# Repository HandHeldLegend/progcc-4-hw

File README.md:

# progcc-4-hw
Official repository for ProGCC 4 Hardware.

## 3D Models License
<br />The 3D CAD files are licensed under a <a rel="license" href="http://creativecommons.org/licenses/by/4.0/">Creative Commons Attribution 4.0 International License</a>.

## Schematic and PCB License
<br />This PCB and electronic schematic are licensed under a <a rel="license" href="http://creativecommons.org/licenses/by-nc-sa/3.0/">Creative Commons Attribution-NonCommercial-ShareAlike 3.0 Unported License</a>.

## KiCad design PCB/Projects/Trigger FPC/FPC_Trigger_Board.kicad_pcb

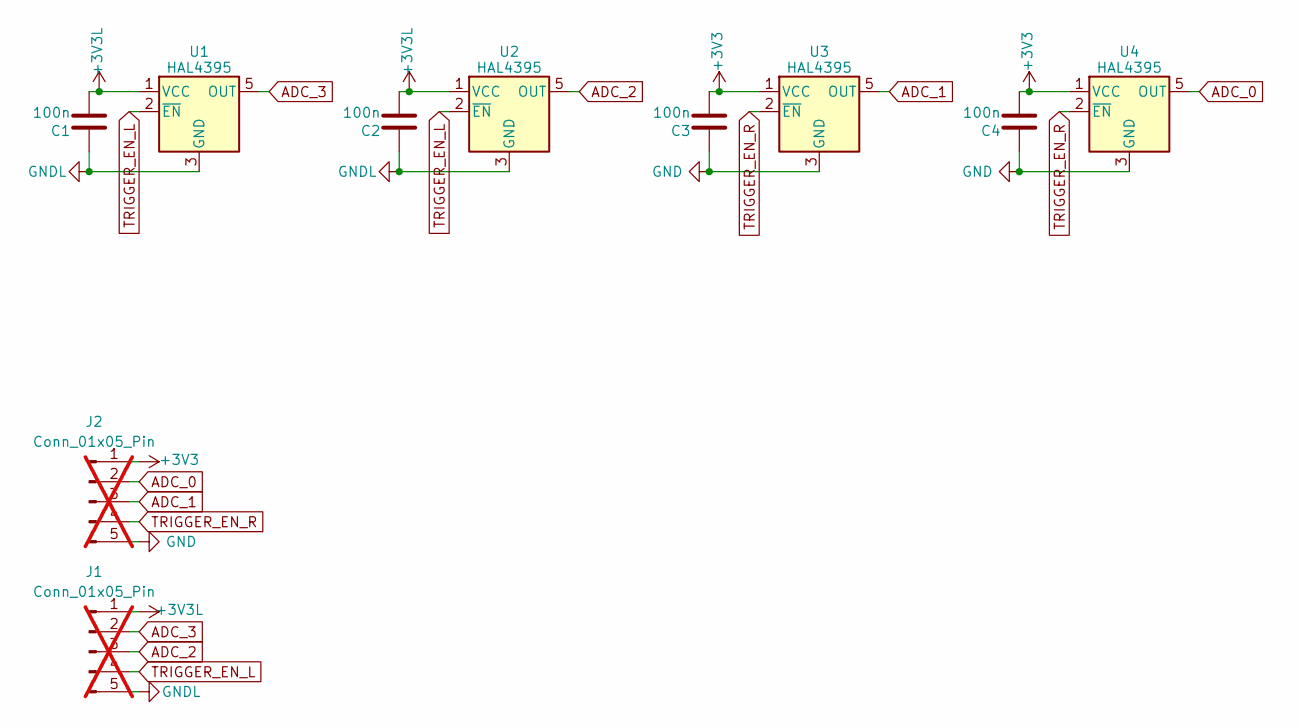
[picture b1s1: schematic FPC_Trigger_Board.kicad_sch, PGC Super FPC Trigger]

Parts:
C1, C2, C3, C4: 100n; C_0201_0603Metric; MPN GRM033R61A104KE15D; LCSC C76934
J1, J2: Conn_01x05_Pin; 505110-0592 Ribbon; not fitted
U1, U2, U3, U4: HAL4395; SOT-23-5L; MPN HAL4395SO5; LCSC C49165022

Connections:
+3V3: C3.2, C4.2, J2.1, U3.1 (VCC), U4.1 (VCC)
+3V3L: C1.2, C2.2, J1.1, U1.1 (VCC), U2.1 (VCC)
ADC_0: J2.2, U4.5 (OUT)
ADC_1: J2.3, U3.5 (OUT)
ADC_2: J1.3, U2.5 (OUT)
ADC_3: J1.2, U1.5 (OUT)
GND: C3.1, C4.1, J2.5, U3.3 (GND), U4.3 (GND)
GNDL: C1.1, C2.1, J1.5, U1.3 (GND), U2.3 (GND)
TRIGGER_EN_L: J1.4, U1.2 (~EN), U2.2 (~EN)
TRIGGER_EN_R: J2.4, U3.2 (~EN), U4.2 (~EN)

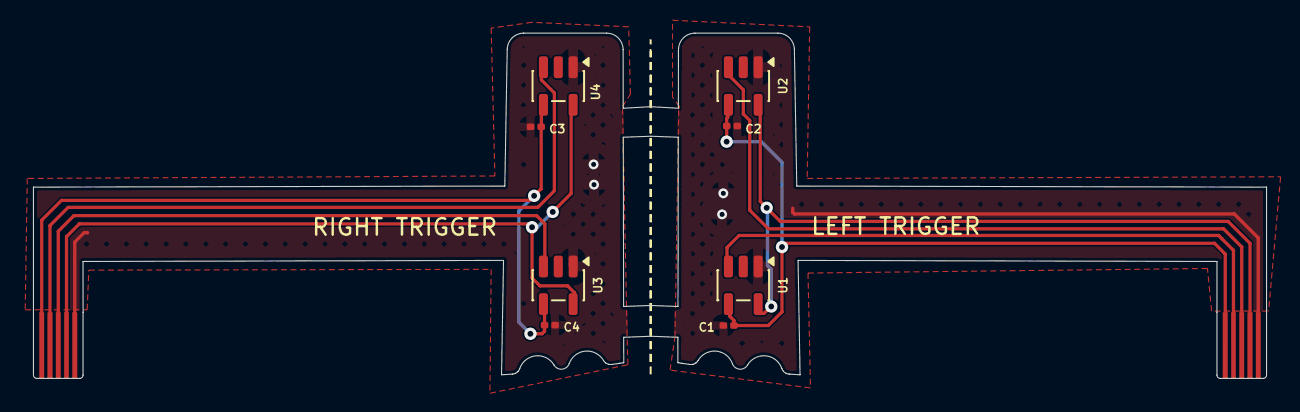
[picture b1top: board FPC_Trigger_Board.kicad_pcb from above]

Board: 2 copper layers, 74.6 x 20.9 mm, 10 parts (2 on the bottom side), 10 nets.

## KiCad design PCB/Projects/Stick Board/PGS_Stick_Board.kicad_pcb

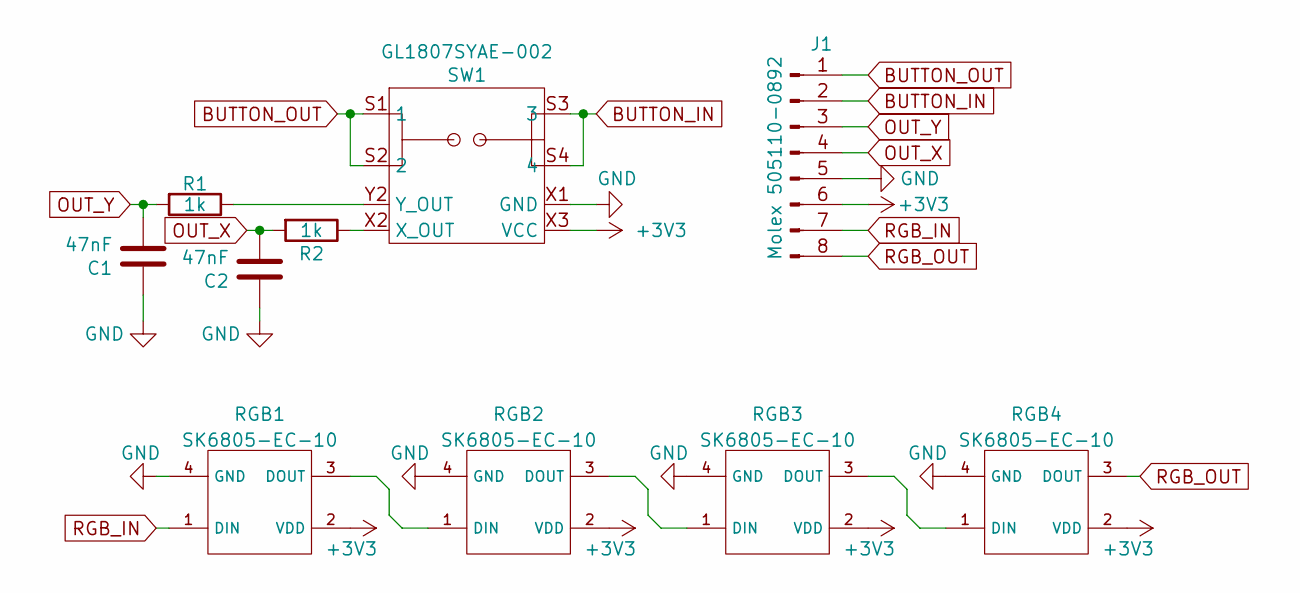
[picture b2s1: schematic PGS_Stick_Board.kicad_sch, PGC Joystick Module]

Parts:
C1, C2: 47nF; C_0402_1005Metric; MPN CC0402KRX7R9BB473; LCSC C272875
J1: Molex 505110-0892; 5051100892; MPN 505110-0892; LCSC C5902847
R1, R2: 1k; R_0201_0603Metric; MPN RC0201FR-071KL; LCSC C138165
RGB1, RGB2, RGB3, RGB4: SK6805-EC-10; MPN SK6805-EC-10; LCSC C22394946
SW1: GL1807SYAE-002; GL1807SYAE; MPN GL1807SYAE-002

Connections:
+3V3: J1.6, RGB1.2 (VDD), RGB2.2 (VDD), RGB3.2 (VDD), RGB4.2 (VDD), SW1.X3 (VCC), SW1.Y3 (VCC)
BUTTON_IN: J1.2, SW1.S3 (3), SW1.S4 (4)
BUTTON_OUT: J1.1, SW1.S1 (1), SW1.S2 (2)
GND: C1.1, C2.1, J1.5, RGB1.4 (GND), RGB2.4 (GND), RGB3.4 (GND), RGB4.4 (GND), SW1.X1 (GND), SW1.Y1 (GND)
unnamed: RGB1.3 (DOUT), RGB2.1 (DIN)
unnamed: RGB2.3 (DOUT), RGB3.1 (DIN)
unnamed: RGB3.3 (DOUT), RGB4.1 (DIN)
unnamed: R2.1, SW1.X2 (X_OUT)
unnamed: R1.1, SW1.Y2 (Y_OUT)
OUT_X: C2.2, J1.4, R2.2
OUT_Y: C1.2, J1.3, R1.2
RGB_IN: J1.7, RGB1.1 (DIN)
RGB_OUT: J1.8, RGB4.3 (DOUT)

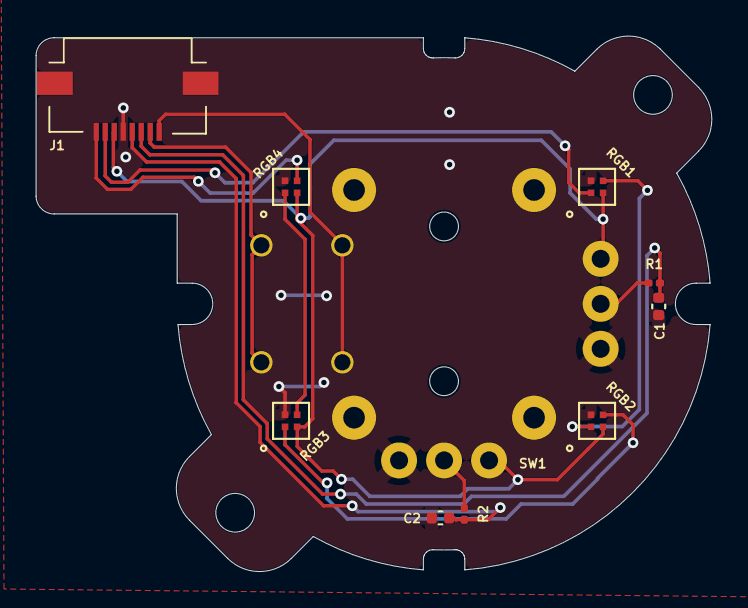
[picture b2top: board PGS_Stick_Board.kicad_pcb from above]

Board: 2 copper layers, 37.5 x 29.7 mm, 10 parts (0 on the bottom side), 13 nets.

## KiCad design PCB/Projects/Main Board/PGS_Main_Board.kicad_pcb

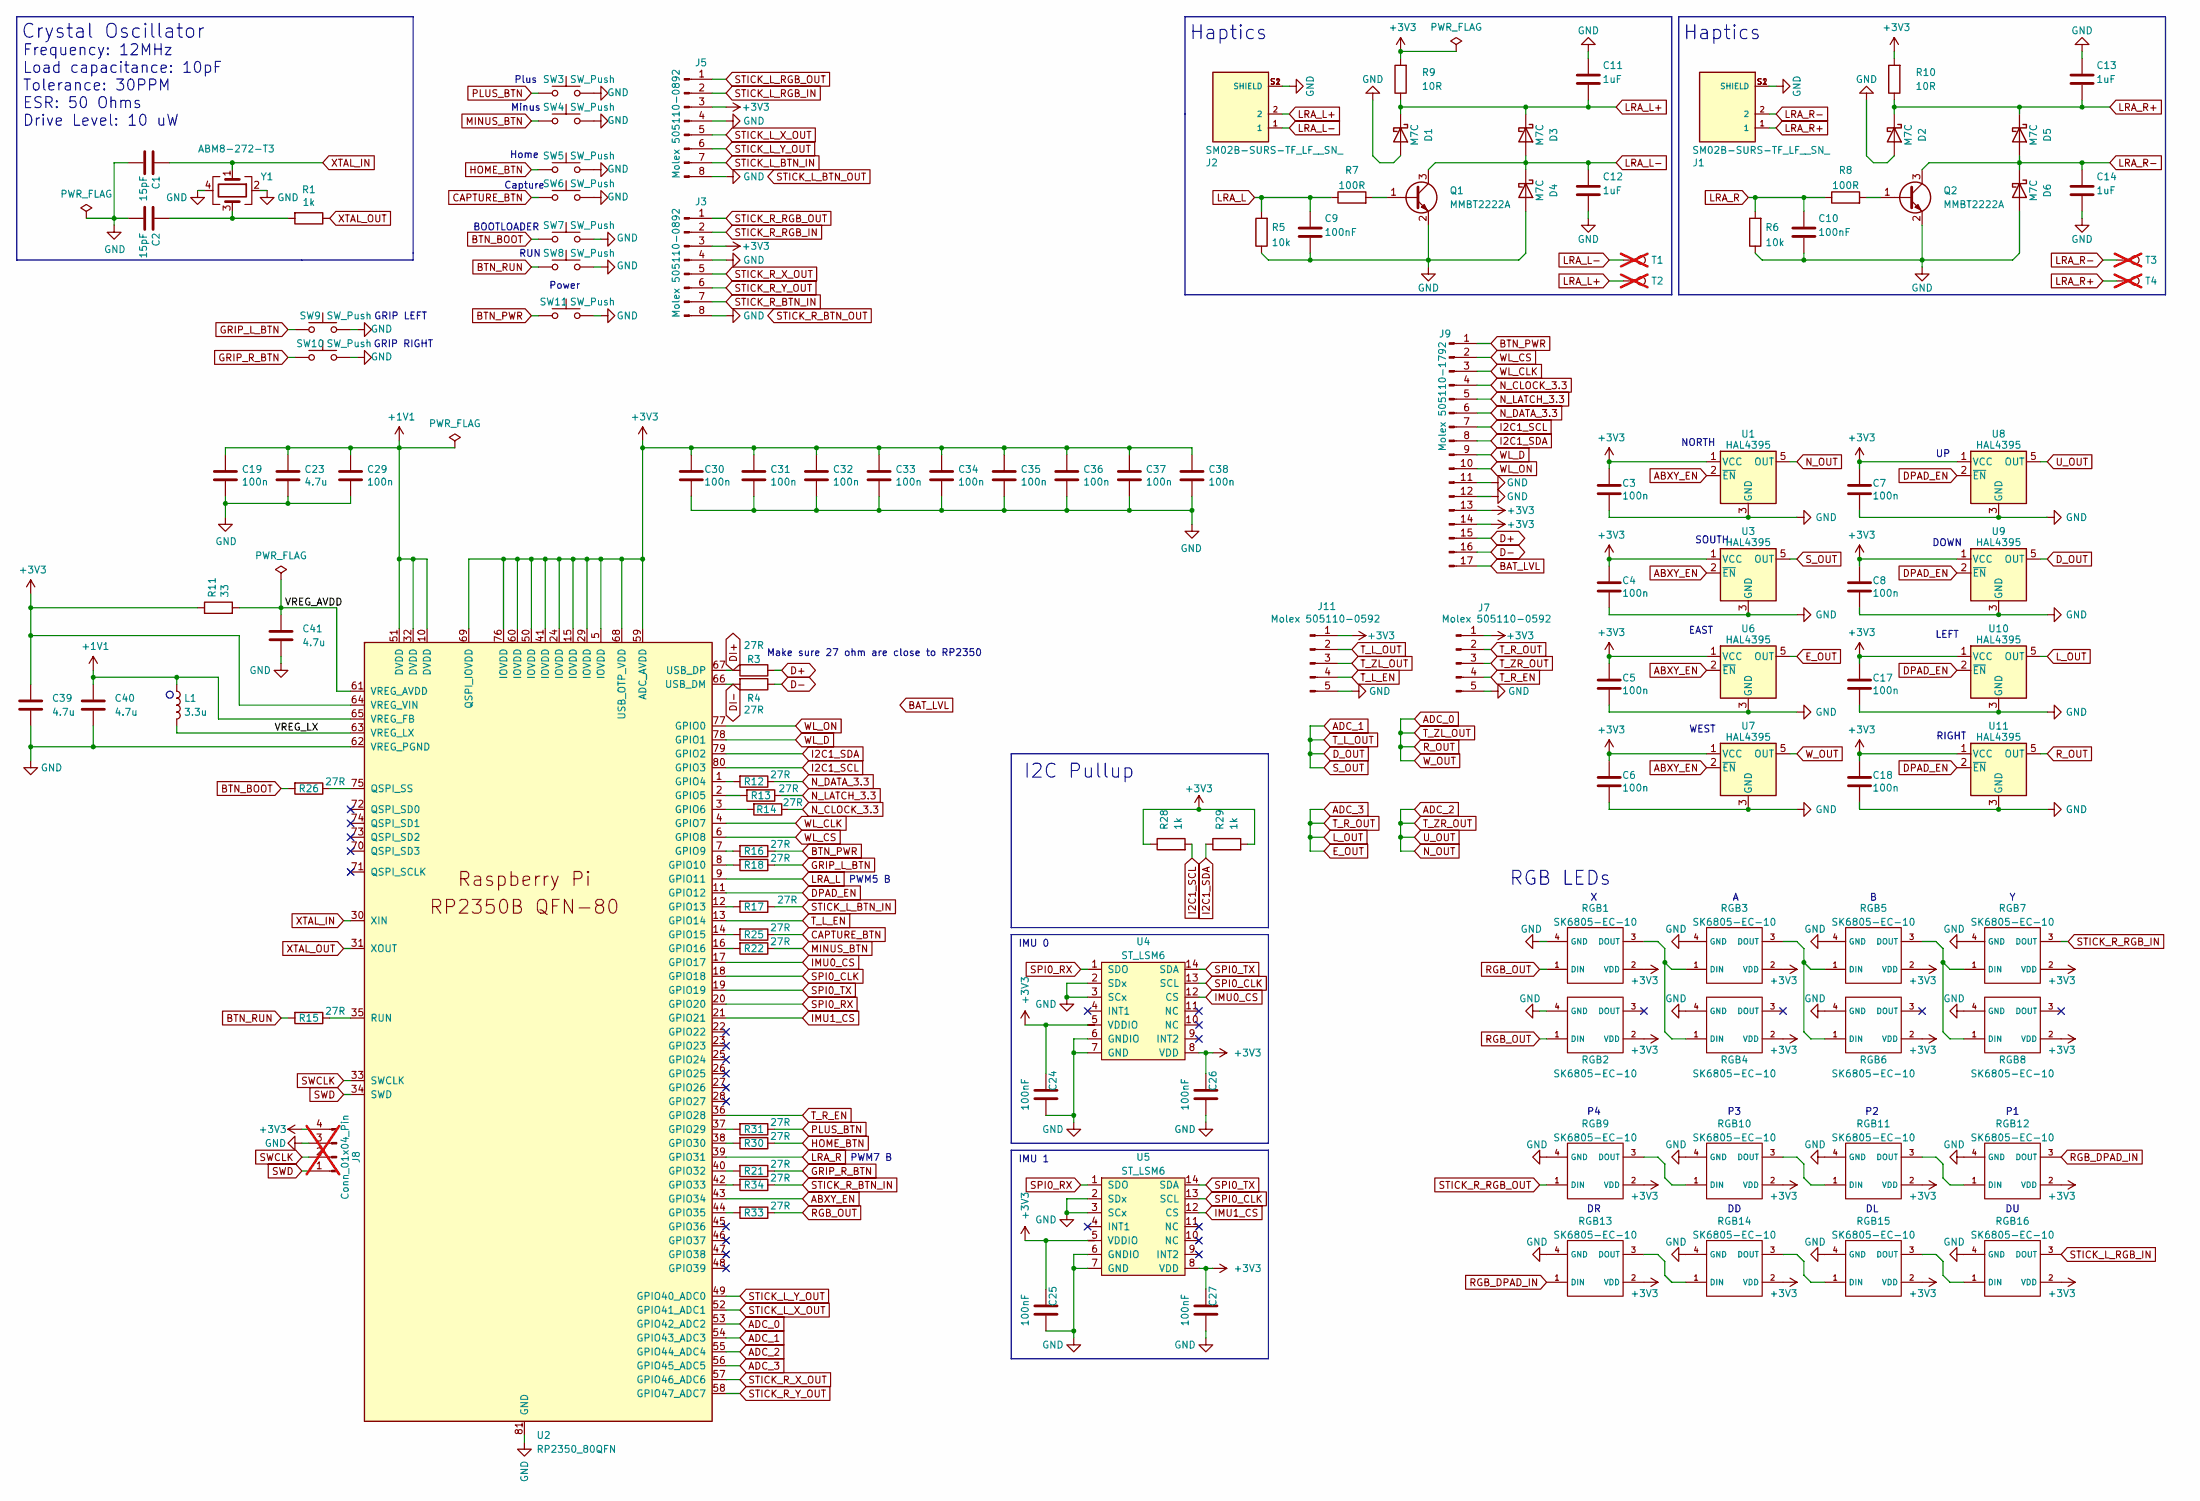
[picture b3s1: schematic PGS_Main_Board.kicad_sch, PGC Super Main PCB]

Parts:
C1, C2: 15pF; C_0402_1005Metric; MPN CC0402FRNPO9BN150; LCSC C326803
C3, C4, C5, C6, C7, C8, C17, C18, C19, C29, C30, C31, C32, C33, C34, C35, C36, C37, C38: 100n; C_0201_0603Metric; MPN GRM033R61A104KE15D; LCSC C76934
C9, C10, C24, C25, C26, C27: 100nF; C_0201_0603Metric; MPN CL03A104KQ3NNNC; LCSC C160831
C11, C12, C13, C14: 1uF; C_0201_0603Metric; MPN GRM033R60J105KEA2D; LCSC C76929
C23, C39, C40, C41: 4.7u; C_0402_1005Metric; MPN CL05A475KP5NRNC; LCSC C368809
D1, D2, D3, D4, D5, D6: M7C; D_SOD-523; MPN B5819WT; LCSC C5364321
J1, J2: SM02B-SURS-TF_LF__SN_; JST_SM02B-SURS-TF_LF__SN_; PARTREV N/A; LCSC C566239
J3, J5: Molex 505110-0892; 5051100892; MPN 505110-0892; LCSC C5902847
J7, J11: Molex 505110-0592; 5051100592; MPN 505110-0592; LCSC C3168457
J8: Conn_01x04_Pin; PinHeader_1x04_P2.00mm_Vertical; not fitted
J9: Molex 505110-1792; 5051101792; MPN 505110-1792; LCSC C6819458
L1: 3.3u; L_pol_2016; MPN AOTA-B201610S3R3-101-T; LCSC C42411119
Q1, Q2: MMBT2222A; SOT-23; MPN MMBT2222A; LCSC C916372
R1, R28, R29: 1k; R_0201_0603Metric; MPN RC0201FR-071KL; LCSC C138165
R3, R4, R12, R13, R14, R15, R16, R17, R18, R21, R22, R25, R26, R30, R31, R33, R34: 27R; R_0201_0603Metric; MPN RC0201FR-0727RL; LCSC C273268
R5, R6: 10k; R_0201_0603Metric; MPN RC0201FR-0710KL; LCSC C106225
R7, R8: 100R; R_0201_0603Metric; MPN RC0201FR-07100RL; LCSC C77623
R9, R10: 10R; R_0201_0603Metric; MPN RC0201FR-0710RL; LCSC C106226
R11: 33; R_0201_0603Metric; MPN RC0201FR-0733RL; LCSC C295794
RGB1, RGB2, RGB3, RGB4, RGB5, RGB6, RGB7, RGB8, RGB9, RGB10, RGB11, RGB12, RGB13, RGB14, RGB15, RGB16: SK6805-EC-10; MPN SK6805-EC-10; LCSC C22394946
SW3, SW4, SW5, SW6, SW7, SW8, SW9, SW10, SW11: SW_Push; KSC-TE; MPN KSC201J LFS; LCSC C221725
T1, T2, T3, T4: PinHeader_1x01_P1.00mm_Vertical; not fitted
U1, U3, U6, U7, U8, U9, U10, U11: HAL4395; SOT-23-5L; MPN HAL4395SO5; LCSC C49165022
U2: RP2350_80QFN; RP2350-QFN-80-1EP_10x10_P0.4mm_EP3.4x3.4mm_ThermalVias; MPN RP2354B; LCSC C39843328
U4, U5: ST_LSM6; LGA14; MPN LSM6DSLTR; LCSC C126672
Y1: ABM8-272-T3; Crystal_SMD_3225-4Pin_3.2x2.5mm; MPN ABM8-272-T3; LCSC C20625731

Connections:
+1V1: C19.1, C23.1, C29.1, C40.1, L1.1, U2.10 (DVDD), U2.32 (DVDD), U2.51 (DVDD), U2.65 (VREG_FB)
+3V3: C3.1, C4.1, C5.1, C6.1, C7.1, C8.1, C17.1, C18.1, C24.2, C25.2, C26.2, C27.2, C30.1, C31.1, C32.1, C33.1, C34.1, C35.1, C36.1, C37.1, C38.1, C39.1, J3.3, J5.3, J7.1, J8.4, J9.13, J9.14, J11.1, R9.2, R10.2, R11.1, R28.1, R29.2, RGB1.2 (VDD), RGB2.2 (VDD), RGB3.2 (VDD), RGB4.2 (VDD), RGB5.2 (VDD), RGB6.2 (VDD), RGB7.2 (VDD), RGB8.2 (VDD), RGB9.2 (VDD), RGB10.2 (VDD), RGB11.2 (VDD), RGB12.2 (VDD), RGB13.2 (VDD), RGB14.2 (VDD), RGB15.2 (VDD), RGB16.2 (VDD), U1.1 (VCC), U2.5 (IOVDD), U2.15 (IOVDD), U2.24 (IOVDD), U2.29 (IOVDD), U2.41 (IOVDD), U2.50 (IOVDD), U2.59 (ADC_AVDD), U2.60 (IOVDD), U2.64 (VREG_VIN), U2.68 (USB_OTP_VDD), U2.69 (QSPI_IOVDD), U2.76 (IOVDD), U3.1 (VCC), U4.5 (VDDIO), U4.8 (VDD), U5.5 (VDDIO), U5.8 (VDD), U6.1 (VCC), U7.1 (VCC), U8.1 (VCC), U9.1 (VCC), U10.1 (VCC), U11.1 (VCC)
/VREG_AVDD: C41.1, R11.2, U2.61 (VREG_AVDD)
/VREG_LX: L1.2, U2.63 (VREG_LX)
ABXY_EN: U1.2 (~EN), U2.43 (GPIO34), U3.2 (~EN), U6.2 (~EN), U7.2 (~EN)
ADC_0: J11.3, U2.53 (GPIO42_ADC2), U7.5 (OUT), U11.5 (OUT)
ADC_1: J11.2, U2.54 (GPIO43_ADC3), U3.5 (OUT), U9.5 (OUT)
ADC_2: J7.3, U1.5 (OUT), U2.55 (GPIO44_ADC4), U8.5 (OUT)
ADC_3: J7.2, U2.56 (GPIO45_ADC5), U6.5 (OUT), U10.5 (OUT)
BAT_LVL: J9.17
BTN_BOOT: R26.2, SW7.1
BTN_PWR: J9.1, R16.1, SW11.1
BTN_RUN: R15.2, SW8.1
CAPTURE_BTN: R25.1, SW6.1
D+: J9.15, R3.1
D-: J9.16, R4.1
DI+: R3.2, U2.67 (USB_DP)
DI-: R4.2, U2.66 (USB_DM)
DPAD_EN: U2.11 (GPIO12), U8.2 (~EN), U9.2 (~EN), U10.2 (~EN), U11.2 (~EN)
GND: C1.2, C2.2, C3.2, C4.2, C5.2, C6.2, C7.2, C8.2, C9.2, C10.2, C11.1, C12.2, C13.1, C14.2, C17.2, C18.2, C19.2, C23.2, C24.1, C25.1, C26.1, C27.1, C29.2, C30.2, C31.2, C32.2, C33.2, C34.2, C35.2, C36.2, C37.2, C38.2, C39.2, C40.2, C41.2, D1.2 (A), D2.2 (A), D4.2 (A), D6.2 (A), J1.S1 (SHIELD), J1.S2 (SHIELD), J2.S1 (SHIELD), J2.S2 (SHIELD), J3.4, J3.8, J5.4, J5.8, J7.5, J8.3, J9.11, J9.12, J11.5, Q1.2 (E), Q2.2 (E), R5.1, R6.1, RGB1.4 (GND), RGB2.4 (GND), RGB3.4 (GND), RGB4.4 (GND), RGB5.4 (GND), RGB6.4 (GND), RGB7.4 (GND), RGB8.4 (GND), RGB9.4 (GND), RGB10.4 (GND), RGB11.4 (GND), RGB12.4 (GND), RGB13.4 (GND), RGB14.4 (GND), RGB15.4 (GND), RGB16.4 (GND), SW3.2, SW4.2, SW5.2, SW6.2, SW7.2, SW8.2, SW9.2, SW10.2, SW11.2, U1.3 (GND), U2.62 (VREG_PGND), U2.81 (GND), U3.3 (GND), U4.2 (SDx), U4.3 (SCx), U4.6 (GNDIO), U4.7 (GND), U5.2 (SDx), U5.3 (SCx), U5.6 (GNDIO), U5.7 (GND), U6.3 (GND), U7.3 (GND), U8.3 (GND), U9.3 (GND), U10.3 (GND), U11.3 (GND), Y1.2, Y1.4
GRIP_L_BTN: R18.1, SW9.1
GRIP_R_BTN: R21.1, SW10.1
HOME_BTN: R30.1, SW5.1
I2C1_SCL: J9.7, R28.2, U2.80 (GPIO3)
I2C1_SDA: J9.8, R29.1, U2.79 (GPIO2)
IMU0_CS: U2.17 (GPIO17), U4.12 (CS)
IMU1_CS: U2.21 (GPIO21), U5.12 (CS)
LRA_L: C9.1, R5.2, R7.1, U2.9 (GPIO11)
LRA_L+: C11.2, D1.1 (K), D3.1 (K), J2.2, R9.1, T2.1 (1_1)
LRA_L-: C12.1, D3.2 (A), D4.1 (K), J2.1, Q1.3 (C), T1.1 (1_1)
LRA_R: C10.1, R6.2, R8.1, U2.39 (GPIO31)
LRA_R+: C13.2, D2.1 (K), D5.1 (K), J1.1, R10.1, T4.1 (1_1)
LRA_R-: C14.1, D5.2 (A), D6.1 (K), J1.2, Q2.3 (C), T3.1 (1_1)
MINUS_BTN: R22.1, SW4.1
N_CLOCK_3.3: J9.4, R14.1
N_DATA_3.3: J9.6, R12.1
N_LATCH_3.3: J9.5, R13.1
unnamed: C2.1, R1.2, Y1.3
unnamed: Q1.1 (B), R7.2
unnamed: Q2.1 (B), R8.2
unnamed: RGB1.3 (DOUT), RGB3.1 (DIN), RGB4.1 (DIN)
unnamed: RGB3.3 (DOUT), RGB5.1 (DIN), RGB6.1 (DIN)
unnamed: RGB5.3 (DOUT), RGB7.1 (DIN), RGB8.1 (DIN)
unnamed: RGB9.3 (DOUT), RGB10.1 (DIN)
unnamed: RGB10.3 (DOUT), RGB11.1 (DIN)
unnamed: RGB11.3 (DOUT), RGB12.1 (DIN)
unnamed: RGB13.3 (DOUT), RGB14.1 (DIN)
unnamed: RGB14.3 (DOUT), RGB15.1 (DIN)
unnamed: RGB15.3 (DOUT), RGB16.1 (DIN)
unnamed: R12.2, U2.1 (GPIO4)
unnamed: R13.2, U2.2 (GPIO5)
unnamed: R14.2, U2.3 (GPIO6)
unnamed: R16.2, U2.7 (GPIO9)
unnamed: R18.2, U2.8 (GPIO10)
unnamed: R17.2, U2.12 (GPIO13)
unnamed: R25.2, U2.14 (GPIO15)
unnamed: R22.2, U2.16 (GPIO16)
unnamed: R31.2, U2.37 (GPIO29)
unnamed: R30.2, U2.38 (GPIO30)
unnamed: R21.2, U2.40 (GPIO32)
unnamed: R34.2, U2.42 (GPIO33)
unnamed: R33.2, U2.44 (GPIO35)
unnamed: R26.1, U2.75 (QSPI_SS)
unnamed: R15.1, U2.35 (RUN)
PLUS_BTN: R31.1, SW3.1
RGB_DPAD_IN: RGB12.3 (DOUT), RGB13.1 (DIN)
RGB_OUT: R33.1, RGB1.1 (DIN), RGB2.1 (DIN)
SPI0_CLK: U2.18 (GPIO18), U4.13 (SCL), U5.13 (SCL)
SPI0_RX: U2.20 (GPIO20), U4.1 (SDO), U5.1 (SDO)
SPI0_TX: U2.19 (GPIO19), U4.14 (SDA), U5.14 (SDA)
STICK_L_BTN_IN: J5.7, R17.1
STICK_L_RGB_IN: J5.2, RGB16.3 (DOUT)
STICK_L_RGB_OUT: J5.1
STICK_L_X_OUT: J5.5, U2.52 (GPIO41_ADC1)
STICK_L_Y_OUT: J5.6, U2.49 (GPIO40_ADC0)
STICK_R_BTN_IN: J3.7, R34.1
STICK_R_RGB_IN: J3.2, RGB7.3 (DOUT)
STICK_R_RGB_OUT: J3.1, RGB9.1 (DIN)
STICK_R_X_OUT: J3.5, U2.57 (GPIO46_ADC6)
STICK_R_Y_OUT: J3.6, U2.58 (GPIO47_ADC7)
SWCLK: J8.2, U2.33 (SWCLK)
SWD: J8.1, U2.34 (SWD)
T_L_EN: J11.4, U2.13 (GPIO14)
T_R_EN: J7.4, U2.36 (GPIO28)
WL_CLK: J9.3, U2.4 (GPIO7)
WL_CS: J9.2, U2.6 (GPIO8)
WL_D: J9.9, U2.78 (GPIO1)
WL_ON: J9.10, U2.77 (GPIO0)
XTAL_IN: C1.1, U2.30 (XIN), Y1.1
XTAL_OUT: R1.1, U2.31 (XOUT)

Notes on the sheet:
Plus
Power
Home
IMU 0
Make sure 27 ohm are close to RP2350
Haptics
RGB LEDs
Crystal Oscillator
GRIP RIGHT
DOWN
GRIP LEFT
SOUTH
IMU 1
Capture
WEST
PWM7 B
I2C Pullup
BOOTLOADER
Frequency: 12MHz Load capacitance: 10pF Tolerance: 30PPM ESR: 50 Ohms Drive Level: 10 uW
PWM5 B
RUN
RIGHT
NORTH
LEFT
EAST
Minus

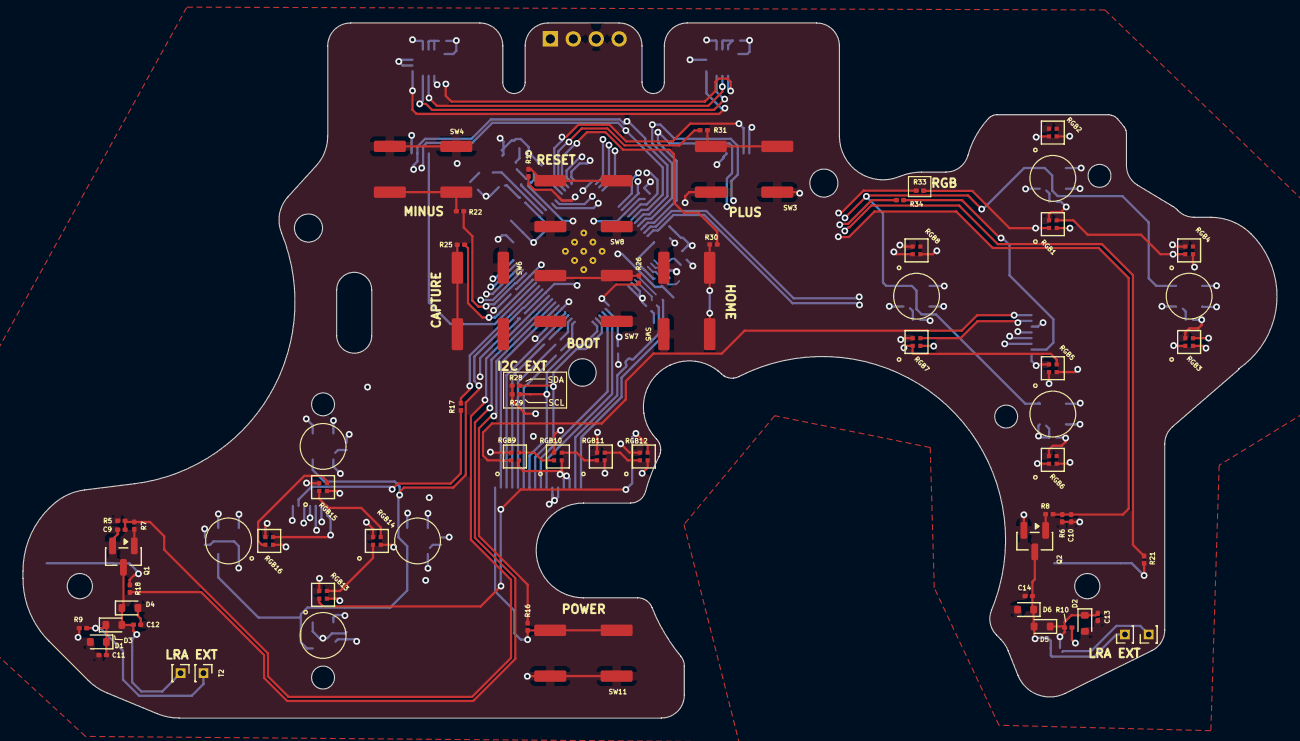
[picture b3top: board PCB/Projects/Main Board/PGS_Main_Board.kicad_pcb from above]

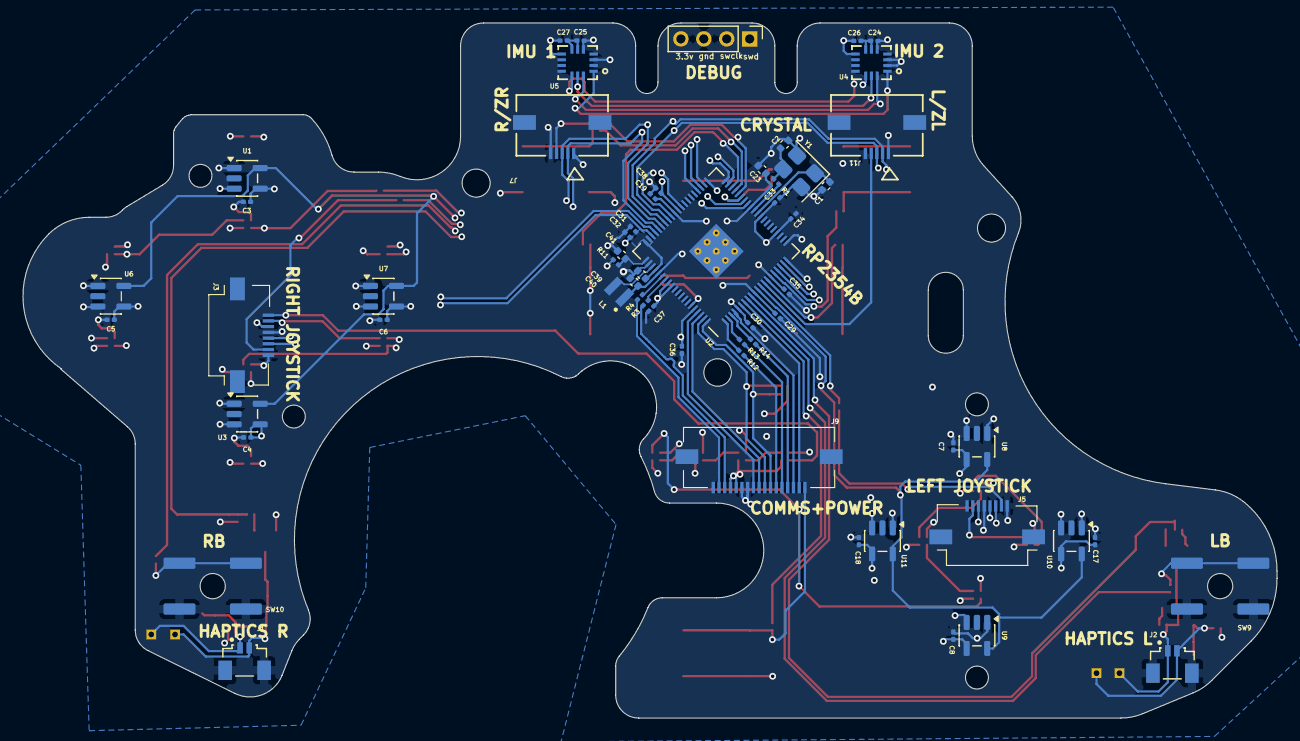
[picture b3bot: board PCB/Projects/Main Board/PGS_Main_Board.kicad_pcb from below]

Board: 4 copper layers, 109.5 x 60.7 mm, 120 parts (59 on the bottom side), 88 nets.

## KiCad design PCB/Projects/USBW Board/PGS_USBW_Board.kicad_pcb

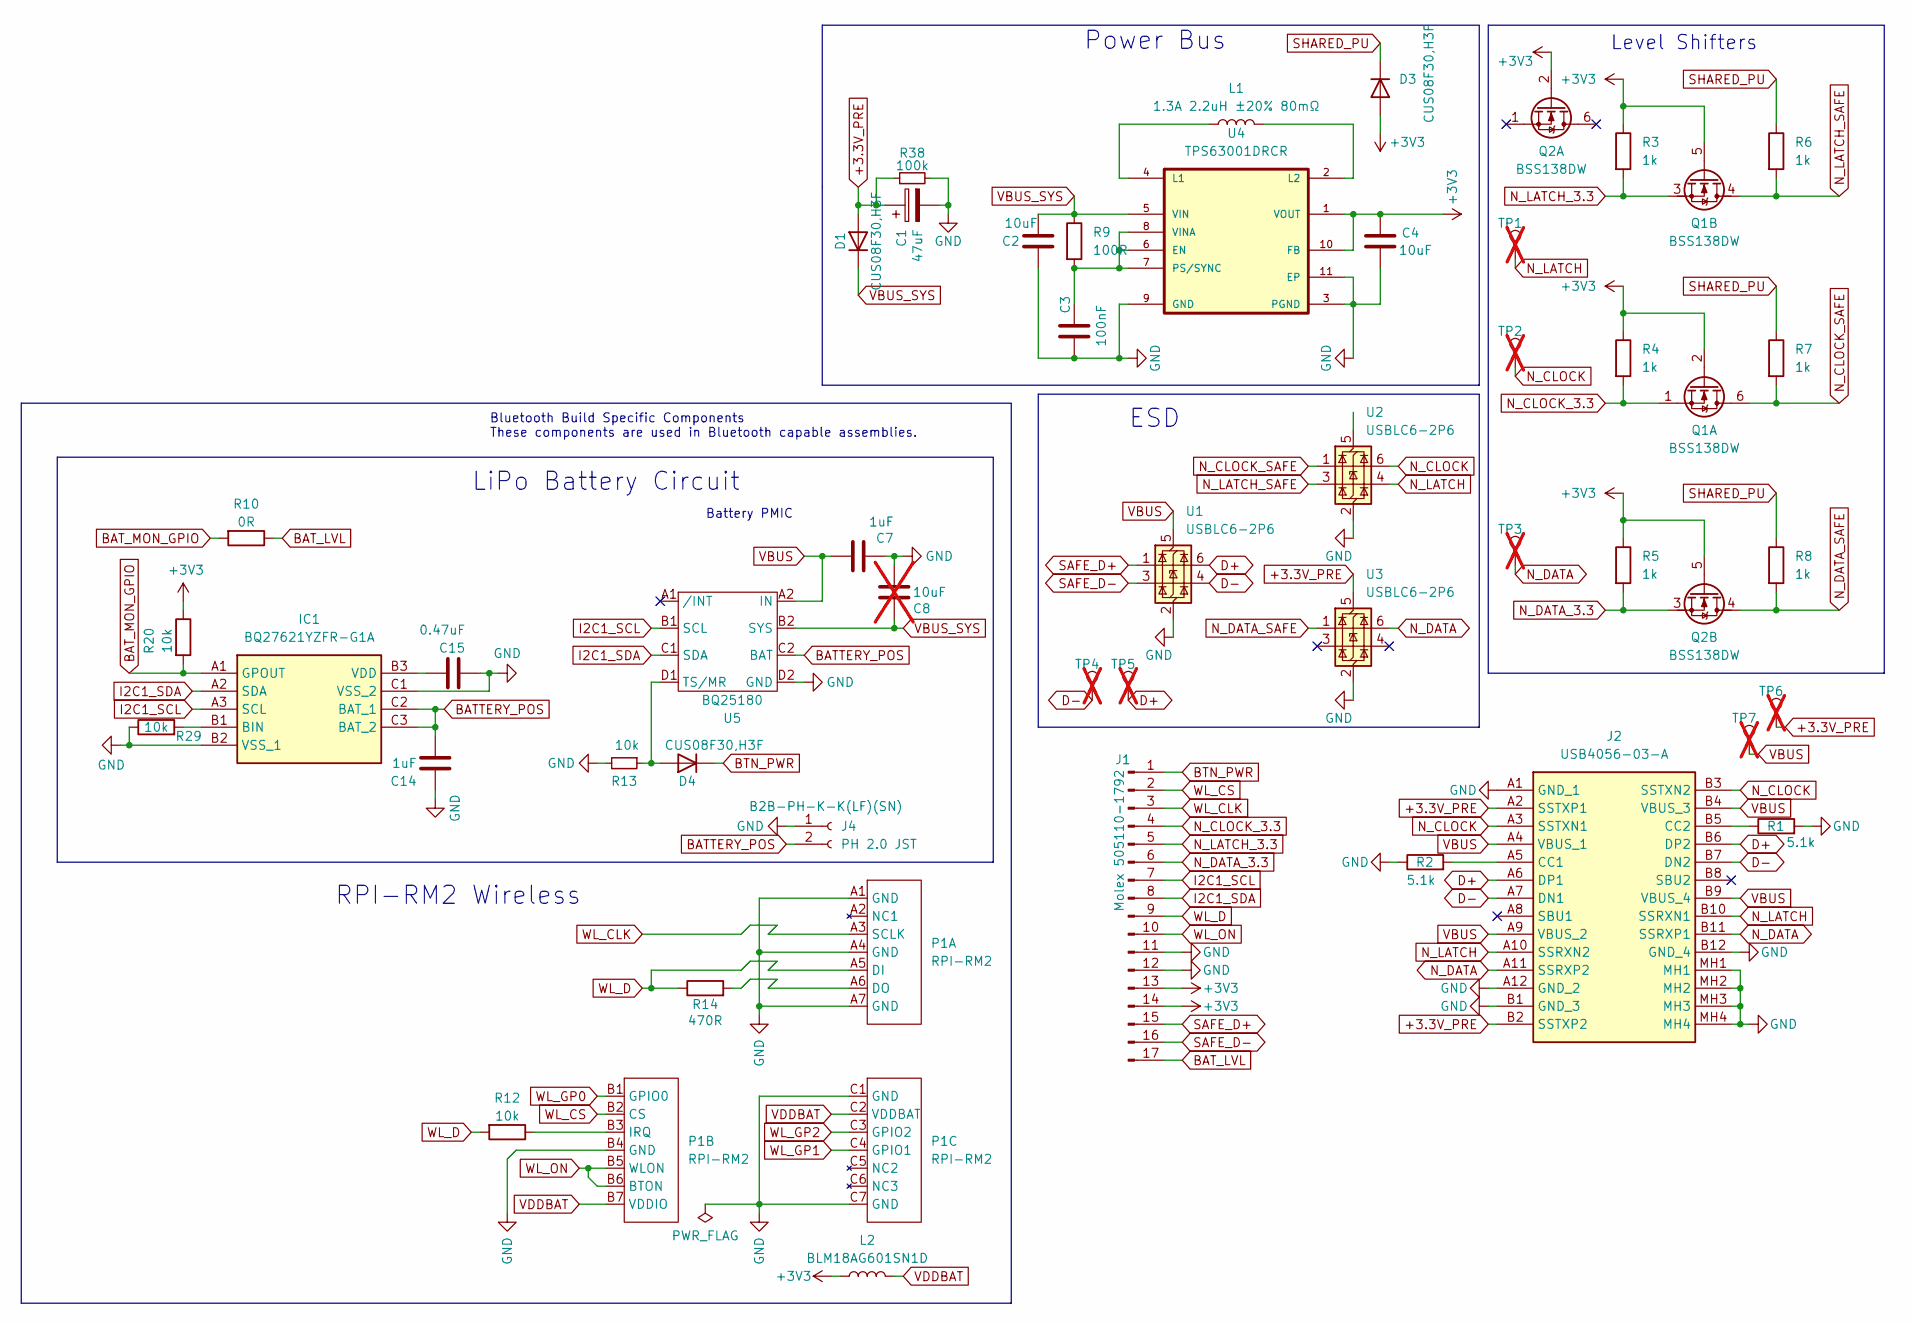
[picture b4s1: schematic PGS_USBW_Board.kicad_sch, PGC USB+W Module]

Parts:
C1: 47uF; CP_EIA-3216-18_Kemet-A; MPN TAJA476K006RNJ; LCSC C7190
C2, C4: 10uF; C_0805_2012Metric; MPN CL21A106KPFNNNE; LCSC C17024
C3: 100nF; C_0201_0603Metric; MPN CL03A104KQ3NNNC; LCSC C160831
C7, C14: 1uF; C_0201_0603Metric; MPN GRM033R60J105KEA2D; LCSC C76929
C8: 10uF; C_0805_2012Metric; MPN CL21A106KPFNNNE; LCSC C17024; not fitted
C15: 0.47uF; C_0201_0603Metric; MPN GRM033R60J474KE90D; LCSC C85926
D1, D3, D4: CUS08F30,H3F; D_SOD-323_HandSoldering; MPN CUS08F30,H3F; LCSC C150183
IC1: BQ27621YZFR-G1A; BGA9C50P3X3_162X158X62; Mouser Part Number 595-BQ27621YZFR-G1A
J1: Molex 505110-1792; 5051101792; MPN 505110-1792; LCSC C6819458
J2: USB4056-03-A; USB405603A; Mouser Part Number 640-USB4056-03-A
J4: PH 2.0 JST; JST_PH_B2B-PH-K_1x02_P2.00mm_Vertical; MPN B2B-PH-K-K(LF)(SN); LCSC C265438
L1: 1.3A 2.2uH ±20% 80mΩ; L_1008_2520Metric; MPN MIP25202R2MBE; LCSC C315721
L2: BLM18AG601SN1D; L_0603_1608Metric; MPN BLM18AG601SN1D; LCSC C19330
P1: RPI-RM2; RPI_RM2; MPN RPI-RM2
Q1, Q2: BSS138DW; SOT-363_SC-70-6; MPN BSS138DW-7-F; LCSC C154900
R1, R2: 5.1k; R_0201_0603Metric; MPN RC0201FR-075K1L; LCSC C274341
R3, R4, R5, R6, R7, R8: 1k; R_0201_0603Metric; MPN RC0201FR-071KL; LCSC C138165
R9: 100R; R_0201_0603Metric; MPN RC0201FR-07100RL; LCSC C77623
R10: 0R; R_0201_0603Metric; MPN RC0201FR-070RL; LCSC C106227
R12, R13, R20, R29: 10k; R_0201_0603Metric; MPN RC0201FR-0710KL; LCSC C106225
R14: 470R; R_0201_0603Metric; MPN AC0201FR-07470RL; LCSC C226558
R38: 100k; R_0402_1005Metric; MPN RC0402FR-07100KL; LCSC C60491
TP1, TP2, TP3, TP4, TP5, TP6, TP7: TestPoint; TestPoint_Pad_D1.0mm; not fitted
U1, U2, U3: USBLC6-2P6; SOT-666; MPN USBLC6-2P6; LCSC C2827693
U4: TPS63001DRCR; VREG_V62_16624-01YE; MPN TPS63001DRCR; LCSC C28060
U5: BQ25180; DSBGA; MPN BQ25180YBGR; LCSC C3682423

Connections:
+3.3V_PRE: C1.1, D1.2 (A), J2.A2 (SSTXP1), J2.B2 (SSTXP2), R38.1, TP6.1 (1_1), U3.5 (VBUS)
+3V3: C4.1, D3.2 (A), J1.13, J1.14, L2.1, Q1.2 (G1), Q1.5 (G2), Q2.2 (G1), Q2.5 (G2), R3.1, R4.1, R5.1, R20.1, U4.1 (VOUT), U4.10 (FB)
BATTERY_POS: C14.2, IC1.C2 (BAT_1), IC1.C3 (BAT_2), J4.2, U5.C2 (BAT)
BAT_LVL: J1.17, R10.1
BAT_MON_GPIO: IC1.A1 (GPOUT), R10.2, R20.2
BTN_PWR: D4.1 (K), J1.1
D+: J2.A6 (DP1), J2.B6 (DP2), TP5.1 (1_1), U1.6 (I/O1)
D-: J2.A7 (DN1), J2.B7 (DN2), TP4.1 (1_1), U1.4 (I/O2)
GND: C1.2, C2.1, C3.1, C4.2, C7.2, C8.1, C14.1, C15.2, IC1.B2 (VSS_1), IC1.C1 (VSS_2), J1.11, J1.12, J2.A1 (GND_1), J2.A12 (GND_2), J2.B1 (GND_3), J2.B12 (GND_4), J2.MH1, J2.MH2, J2.MH3, J2.MH4, J4.1, P1.A1 (GND), P1.A4 (GND), P1.A7 (GND), P1.B4 (GND), P1.C1 (GND), P1.C7 (GND), R1.2, R2.1, R13.2, R29.1, R38.2, U1.2 (GND), U2.2 (GND), U3.2 (GND), U4.3 (PGND), U4.9 (GND), U4.11 (EP), U5.D2 (GND)
I2C1_SCL: IC1.A3 (SCL), J1.7, U5.B1 (SCL)
I2C1_SDA: IC1.A2 (SDA), J1.8, U5.C1 (SDA)
N_CLOCK: J2.A3 (SSTXN1), J2.B3 (SSTXN2), TP2.1 (1_1), U2.6 (I/O1)
N_CLOCK_3.3: J1.4, Q1.1 (S1), R4.2
N_CLOCK_SAFE: Q1.6 (D1), R7.2, U2.1 (I/O1)
N_DATA: J2.A11 (SSRXP2), J2.B11 (SSRXP1), TP3.1 (1_1), U3.6 (I/O1)
N_DATA_3.3: J1.6, Q2.3 (D2), R5.2
N_DATA_SAFE: Q2.4 (S2), R8.2, U3.1 (I/O1)
N_LATCH: J2.A10 (SSRXN2), J2.B10 (SSRXN1), TP1.1 (1_1), U2.4 (I/O2)
N_LATCH_3.3: J1.5, Q1.3 (D2), R3.2
N_LATCH_SAFE: Q1.4 (S2), R6.2, U2.3 (I/O2)
unnamed: D4.2 (A), R13.1, U5.D1 (TS/MR)
unnamed: IC1.B1 (BIN), R29.2
unnamed: C15.1, IC1.B3 (VDD)
unnamed: J2.A5 (CC1), R2.2
unnamed: J2.B5 (CC2), R1.1
unnamed: P1.A6 (DO), R14.2
unnamed: P1.B3 (IRQ), R12.1
unnamed: C3.2, R9.2, U4.6 (EN), U4.7 (PS/SYNC), U4.8 (VINA)
unnamed: L1.1, U4.4 (L1)
unnamed: L1.2, U4.2 (L2)
SAFE_D+: J1.15, U1.1 (I/O1)
SAFE_D-: J1.16, U1.3 (I/O2)
SHARED_PU: D3.1 (K), R6.1, R7.1, R8.1
VBUS: C7.1, J2.A4 (VBUS_1), J2.A9 (VBUS_2), J2.B4 (VBUS_3), J2.B9 (VBUS_4), TP7.1 (1_1), U1.5 (VBUS), U5.A2 (IN)
VBUS_SYS: C2.2, C8.2, D1.1 (K), R9.1, U4.5 (VIN), U5.B2 (SYS)
VDDBAT: L2.2, P1.B7 (VDDIO), P1.C2 (VDDBAT)
WL_CLK: J1.3, P1.A3 (SCLK)
WL_CS: J1.2, P1.B2 (CS)
WL_D: J1.9, P1.A5 (DI), R12.2, R14.1
WL_GP0: P1.B1 (GPIO0)
WL_GP1: P1.C4 (GPIO1)
WL_GP2: P1.C3 (GPIO2)
WL_ON: J1.10, P1.B5 (WLON), P1.B6 (BTON)

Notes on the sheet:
Level Shifters
LiPo Battery Circuit
Battery PMIC
ESD
Power Bus
Bluetooth Build Specific Components These components are used in Bluetooth capable assemblies.
RPI-RM2 Wireless

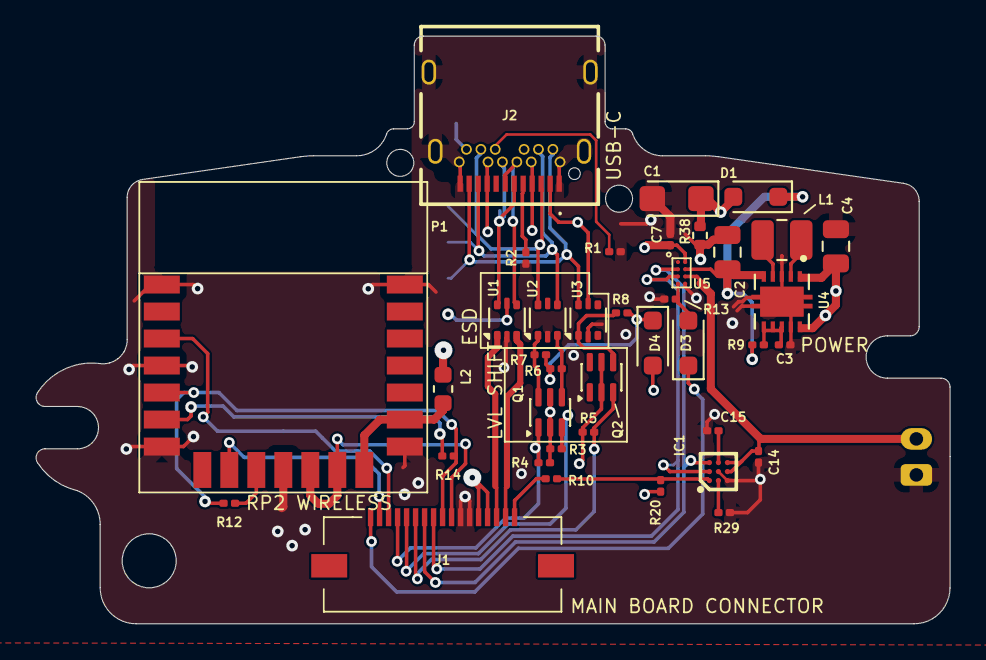
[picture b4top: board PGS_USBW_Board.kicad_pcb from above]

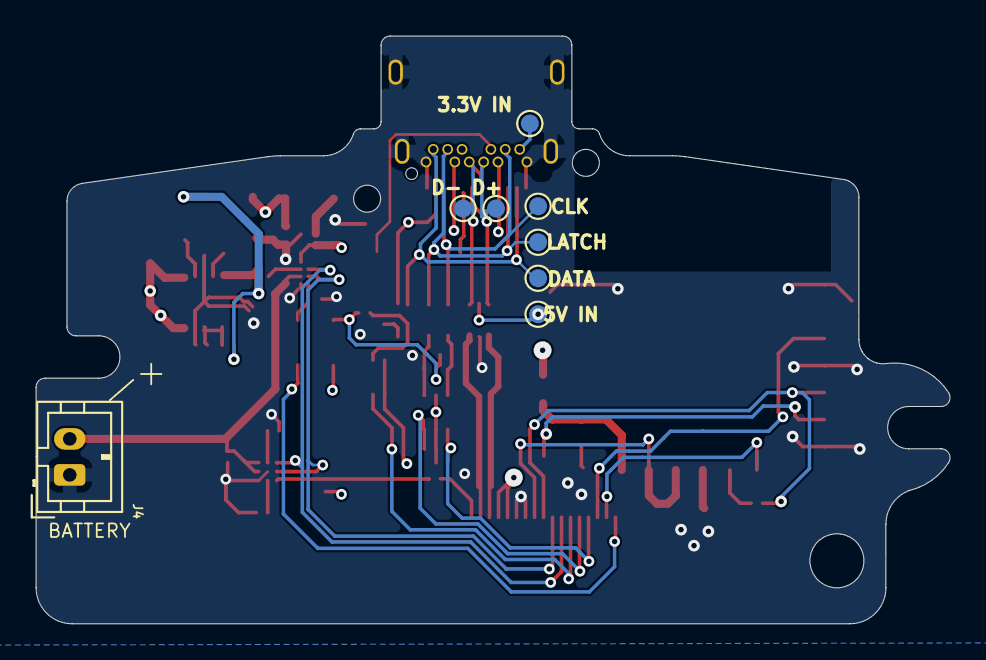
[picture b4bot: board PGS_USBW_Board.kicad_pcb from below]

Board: 4 copper layers, 50.8 x 32.6 mm, 47 parts (8 on the bottom side), 40 nets.

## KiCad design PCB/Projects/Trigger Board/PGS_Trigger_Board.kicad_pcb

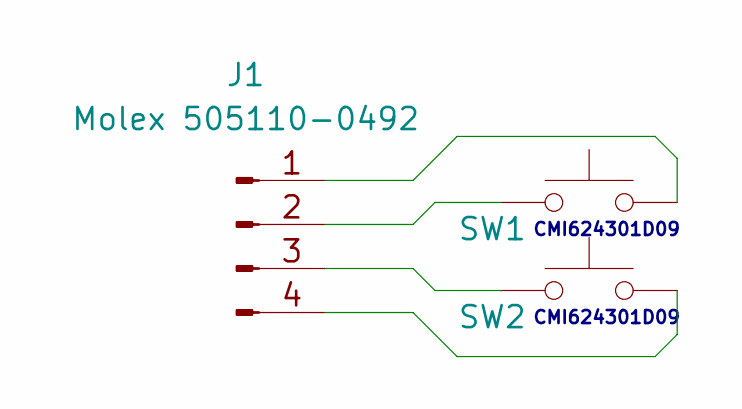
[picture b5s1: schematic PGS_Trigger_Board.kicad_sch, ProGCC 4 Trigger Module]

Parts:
J1: Molex 505110-0492; 5051100492; MPN 505110-0492; LCSC C588007
SW1, SW2: CMI624301D09; EVQP0; MPN CMI624301D09

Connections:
unnamed: J1.1, SW1.2
unnamed: J1.2, SW1.1
unnamed: J1.3, SW2.1
unnamed: J1.4, SW2.2

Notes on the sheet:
CMI624301D09

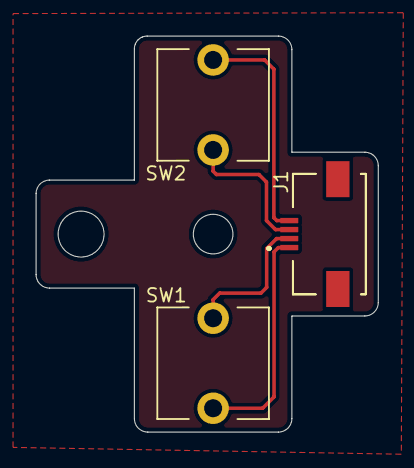
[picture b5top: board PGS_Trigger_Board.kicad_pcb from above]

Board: 2 copper layers, 19.0 x 22.0 mm, 3 parts (0 on the bottom side), 4 nets.
